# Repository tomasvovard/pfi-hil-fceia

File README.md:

# OHSIM: simulación en tiempo real de un convertidor buck

Repositorio del Proyecto Final de Ingeniería Electrónica (FCEIA, Universidad Nacional de Rosario) sobre la puesta en marcha de la plataforma de *hardware-in-the-loop* **OHSIM** y su validación con un modelo de convertidor buck.

OHSIM es una placa con una FPGA AMD Spartan-7 XC7S50 y DAC de 12 bits, diseñada originalmente por Pablo Trujillo, que ejecuta en tiempo real el modelo de un convertidor de potencia y presenta sus variables como tensiones analógicas. En este trabajo se rediseñó y fabricó la placa, se implementó en la FPGA un modelo no ideal del buck (pérdidas e inductancia dependiente de la corriente, paso de 200 ns), se automatizaron los ensayos con una LaunchPad F28379D y se comparó la respuesta de OHSIM con la del modelo simulado en Simulink y con la del convertidor real del laboratorio (CEuP). En el ensayo E1a, el fit de v<sub>o</sub> entre OHSIM y el modelo es de 93,5 %, y entre OHSIM y el convertidor real, de 83,4 %.

## Contenido

| Carpeta | Contenido | Herramientas |
|---|---|---|
| [`hardware/`](hardware/) | Proyecto KiCad de la placa (esquemáticos 3.2, PCB 3.0) y salidas de fabricación | KiCad 9.0 |
| [`fpga/`](fpga/) | Modelo del buck en Verilog, bancos de prueba, restricciones y scripts de Vivado | Vivado 2025.2, Python 3 |
| [`firmware/`](firmware/) | Firmware de la LaunchPad que genera el PWM y ejecuta los ensayos, y herramientas de la PC | CCS 12.8.1, compilador C2000 22.6.1, PowerShell |
| [`matlab/`](matlab/) | Modelo de referencia en Simulink, generador de coeficientes y procesamiento de capturas | MATLAB R2024b, Simulink 24.2 |
| [`data/`](data/) | Capturas del ensayo E1a (CEuP y OHSIM) | |

Cada carpeta tiene su README con el contenido, los pasos de uso y el resultado esperado.

El archivo de configuración de la FPGA utilizado en los ensayos (`.bit`), el archivo de sondas del ILA (`.ltx`), los informes de compilación y sus sumas SHA-256 están en el *release* **candidate-2026-09-11**.

## Herramientas y versiones

| Herramienta | Uso |
|---|---|
| KiCad 9.0 | Esquemáticos y PCB |
| Vivado 2025.2 | Simulación, síntesis, implementación, programación de la FPGA e ILA |
| Python 3, sin bibliotecas adicionales | Vectores de referencia de los bancos de prueba y pruebas del host |
| Code Composer Studio 12.8.1, compilador C2000 22.6.1 LTS | Firmware de la LaunchPad (el subconjunto necesario de C2000Ware 5.04 está incluido) |
| Windows PowerShell 5.1 | Ejecución de los ensayos |
| MATLAB R2024b, Simulink 24.2 | Modelo de referencia, coeficientes y procesamiento |
| System Identification Toolbox, Control System Toolbox | Identificación de funciones de transferencia |
| Programador JTAG (Digilent JTAG-HS3) | Programación de la FPGA y descarga del ILA |
| Osciloscopio de cuatro canales | Captura de las salidas de OHSIM y del CEuP |

Una versión distinta puede funcionar, pero conviene verificarla con los bancos de prueba y con el ensayo E1a antes de comparar resultados.

## Inicio rápido

Sin hardware, se puede comprobar el diseño y reproducir el procesamiento:

1. **FPGA**: desde `fpga/`, `vivado -mode batch -source scripts/validate_all.tcl` corre los siete bancos de prueba, que deben informar `PASS`.
2. **MATLAB**: con `matlab/` como carpeta de trabajo, ejecutar `p4_2_comparar_fuentes_sin_offset` y `p6_identificar_ft` sobre las capturas de E1a y comparar con los resultados esperados de [`matlab/README.md`](matlab/README.md#resultados-esperados-con-e1a).
3. **Host**: desde `firmware/`, `py -m unittest discover -s host`.

Con la plataforma, el orden de trabajo es programar la FPGA con el archivo del *release* ([`fpga/`](fpga/README.md#programación-y-captura-con-el-ila)), cargar el firmware en la LaunchPad respetando la secuencia de encendido ([`firmware/`](firmware/README.md)), ejecutar los ensayos con `host/ohsim_run.ps1` y procesar las capturas en [`matlab/`](matlab/).

## Clonar una sola parte

Para descargar solo una carpeta (por ejemplo, `fpga/`) sin el resto del repositorio:

```
git clone --filter=blob:none --sparse https://github.com/tomasvovard/pfi-hil-fceia.git
cd pfi-hil-fceia
git sparse-checkout set fpga
```

Para agregar otra carpeta más tarde, `git sparse-checkout add matlab data`. Sin Git, cada carpeta puede descargarse desde la página del repositorio.

## Autoría y licencias

Autor: Tomás Vovard. El diseño original de OHSIM es de Pablo Trujillo ([controlpaths.com](https://controlpaths.com/)); la procedencia de cada parte y los agradecimientos están en [`AUTHORS.md`](AUTHORS.md).

- Software, scripts, documentación y datos: [MIT](LICENSE).
- Hardware (`hardware/`): [CERN-OHL-S-2.0](hardware/LICENSE).
- Archivos de terceros (C2000Ware de Texas Instruments y bibliotecas de KiCad en `hardware/lib/`): su licencia original.

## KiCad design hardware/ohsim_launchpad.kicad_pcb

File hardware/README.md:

# Hardware: placa OHSIM (Platform Board)

Proyecto KiCad de la placa de simulación en tiempo real (*hardware-in-the-loop*) OHSIM, basada en una FPGA AMD Spartan-7 XC7S50 (encapsulado FTGB196, que admite desde la XC7S15 hasta la XC7S50). La placa tiene 16 salidas analógicas de 12 bits (dos DAC AD5328 de ocho canales con buffers), entradas y salidas digitales y de PWM y un RP2040 para la administración de la plataforma. Se conecta a placas de desarrollo comerciales para ensayar lazos de control sobre modelos de convertidores:

- Arduino MKR / Portenta
- Raspberry Pi Pico (1 y 2)
- Texas Instruments LaunchPad (en este trabajo se usó la LAUNCHXL-F28379D)

| Cara superior | Cara inferior |
|---|---|
|  |  |

## Origen y revisión

El diseño original es la *Platform Board* del proyecto OHSIM (versión 0.1 en su serigrafía) de Pablo Trujillo ([controlpaths.com](https://controlpaths.com/)). Esta carpeta contiene su rediseño, hecho en este proyecto final. La procedencia y las licencias se detallan en [`AUTHORS.md`](../AUTHORS.md).

- **Esquemáticos: revisión 3.2.** Las revisiones 3.1 y 3.2 solo reorganizan los esquemáticos (rótulo, títulos por hoja y hoja raíz) y no cambian el netlist.
- **PCB: revisión 3.0**, la fabricada y ensayada. El PCB de esta carpeta agrega en la serigrafía inferior la leyenda "Basado en el diseño original de Pablo Trujillo (controlpaths.com)". No cambia el cobre y el DRC da los mismos resultados que el de la placa fabricada, por lo que es eléctricamente idéntico.
- Las salidas de [`fabricacion/`](fabricacion/) son las que se enviaron al fabricante para la placa 3.0 y, por lo tanto, **no incluyen esa leyenda**. Para fabricar una placa con la leyenda, regenerarlas desde KiCad (ver [Uso](#uso)).

## Contenido

| Archivo | Contenido |
|---|---|
| `ohsim_launchpad.kicad_pro` | Proyecto KiCad |
| `ohsim_launchpad.kicad_sch` | Hoja raíz (diagrama general) |
| `supply.kicad_sch` | Fuentes de alimentación (3V3, 1V8, 1V0) |
| `fpga_power.kicad_sch` | FPGA: alimentación, configuración y JTAG |
| `fpga_bank.kicad_sch` | FPGA: bancos de E/S |
| `rp2040.kicad_sch` | Microcontrolador RP2040, memoria flash y microSD |
| `dac.kicad_sch`, `dac1.kicad_sch` | DAC 0 y DAC 1 con buffers (AOUT0 a AOUT7 y AOUT8 a AOUT15) |
| `arduino.kicad_sch`, `rp_pico.kicad_sch`, `ti_launchpad.kicad_sch` | Interfaces con las placas de desarrollo |
| `ohsim_launchpad.kicad_pcb` | PCB de cuatro capas |
| `ohsim_rotulo.kicad_wks` | Rótulo de las hojas del esquemático |
| `ohsim_launchpad.pdf` | Esquemáticos en PDF |
| `lib/` | Símbolos, huellas y modelos 3D que no forman parte de las bibliotecas estándar de KiCad (ver [Bibliotecas de terceros](#bibliotecas-de-terceros)) |
| `fabricacion/` | Gerbers y perforaciones (`ohsim_launchpad.zip`), BOM, posiciones de montaje (CPL), designadores y netlist IPC de la placa fabricada |
| `img/` | Renders de la placa y logos usados en la serigrafía |

## Uso

Herramienta: **KiCad 9.0**. Las bibliotecas propias se referencian con `${KIPRJMOD}`, de modo que el proyecto abre desde cualquier ubicación sin configurar rutas. Los modelos 3D estándar se toman de las variables `KICAD8_3DMODEL_DIR` y `KICAD9_3DMODEL_DIR` de la instalación de KiCad. La serigrafía usa la fuente Orbitron; si no está instalada, KiCad la reemplaza en pantalla, pero los Gerbers deben generarse con ella instalada.

1. Abrir `ohsim_launchpad.kicad_pro` con KiCad 9.
2. Para revisar el diseño, correr el ERC en el editor de esquemáticos y el DRC en el editor de PCB. El DRC informa cinco observaciones conocidas y aceptadas (cuatro solapamientos de serigrafía y una huella de tipo pasante con pads SMD) y ningún pad sin conectar.
3. Para regenerar las salidas de fabricación, usar *Archivo → Salidas de fabricación* (Gerber, perforaciones, BOM y posiciones), o desde la línea de comandos:

```
kicad-cli pcb export gerbers -o salidas/ ohsim_launchpad.kicad_pcb
kicad-cli pcb export drill -o salidas/ ohsim_launchpad.kicad_pcb
kicad-cli pcb export pos --format csv --units mm -o salidas/posiciones.csv ohsim_launchpad.kicad_pcb
```

La BOM de `fabricacion/bom.csv` incluye la columna `LCSC Part #` con los números de parte usados en el ensamblado. La FPGA (U1) figura como XC7S50-1FTGB196C, la de la placa ensayada, sin número de parte LCSC; la BOM original del pedido la listaba como XC7S25.

## Historial de revisiones

### 3.2 (esquemáticos)
- Rótulo nuevo, títulos descriptivos por hoja y reorganización visual de la hoja raíz. La hoja de alimentación pasa a formato A4. Sin cambios eléctricos.
- PCB: leyenda de atribución al diseño original en la serigrafía inferior. Sin cambios en el cobre.

### 3.0 (PCB fabricado)
- Se unificaron los encapsulados de los componentes eléctricamente iguales y se rehízo la cara inferior priorizando caminos cortos a GND en los capacitores de desacople.
- Se revisaron y completaron los números de parte LCSC y los encapsulados de todos los componentes.
- Se cableó la señal DONE_RP2040 con R69 (0 Ω, no montada) para futuras versiones del firmware del microcontrolador.
- Se reemplazaron los conectores RJ45 por tiras de pines macho de 2 × 4 con paso de 2,54 mm, con todas las señales analógicas rodeadas por GND.
- Se agregaron puntos de prueba con la distribución de una punta de osciloscopio con resorte de GND (Rigol PVP2350).
- Se quitó el recubrimiento de las vías de PWM y de los buses de tensión para usarlas como puntos de prueba, con vías de GND descubiertas cercanas.
- Se agregó la serigrafía de la Universidad, la Facultad, la cátedra y el autor del rediseño.

### 2
- Pistas de alimentación de la FPGA de 0,2 mm de ancho.
- Huellas de componentes pasivos entre 0603 y 0805.
- Vías reubicadas para que no interfieran con los pads de soldadura.

### 1
- Vías debajo de la FPGA reubicadas para que no interfieran con los pads de soldadura.

## Bibliotecas de terceros

La carpeta `lib/` incluye bibliotecas y modelos de terceros, en su mayoría heredados del diseño original. No están cubiertos por la licencia de esta carpeta y conservan la de su autor:

| Archivos | Origen |
|---|---|
| `arduino-library.kicad_sym`, `arduino-library.pretty/` | Biblioteca KiCad de placas Arduino |
| `ABX00042.kicad_sym`, `MODULE_ABX00042.kicad_mod` | Arduino Portenta H7 (ABX00042, SnapEDA) |
| `MCU_RaspberryPi_and_Boards.kicad_sym`, `MCU_RaspberryPi_and_Boards.pretty/`, `Pico.wrl` | Biblioteca KiCad para Raspberry Pi Pico de Nicolò Carandini |
| `LAUNCHXL-F28379D.kicad_sym`, `MOD_LAUNCHXL-F28379D.kicad_mod` | LaunchPad LAUNCHXL-F28379D de Texas Instruments (SnapEDA) |
| `xilinx7.lib` | Símbolos de la familia Xilinx 7 |
| `DM3AT-SF-PEJM5--3DModel-STEP-418109.STEP` | Modelo de fabricante (Hirose) |
| `LQH3NPN2R2MMEL.step`, `IND_LQH3NPN2R2MMEL.kicad_mod` | Modelo y huella de fabricante (Murata) |

## Licencia

El diseño de hardware de esta carpeta se distribuye bajo la licencia [CERN-OHL-S-2.0](LICENSE). Las bibliotecas de terceros mantienen la suya.

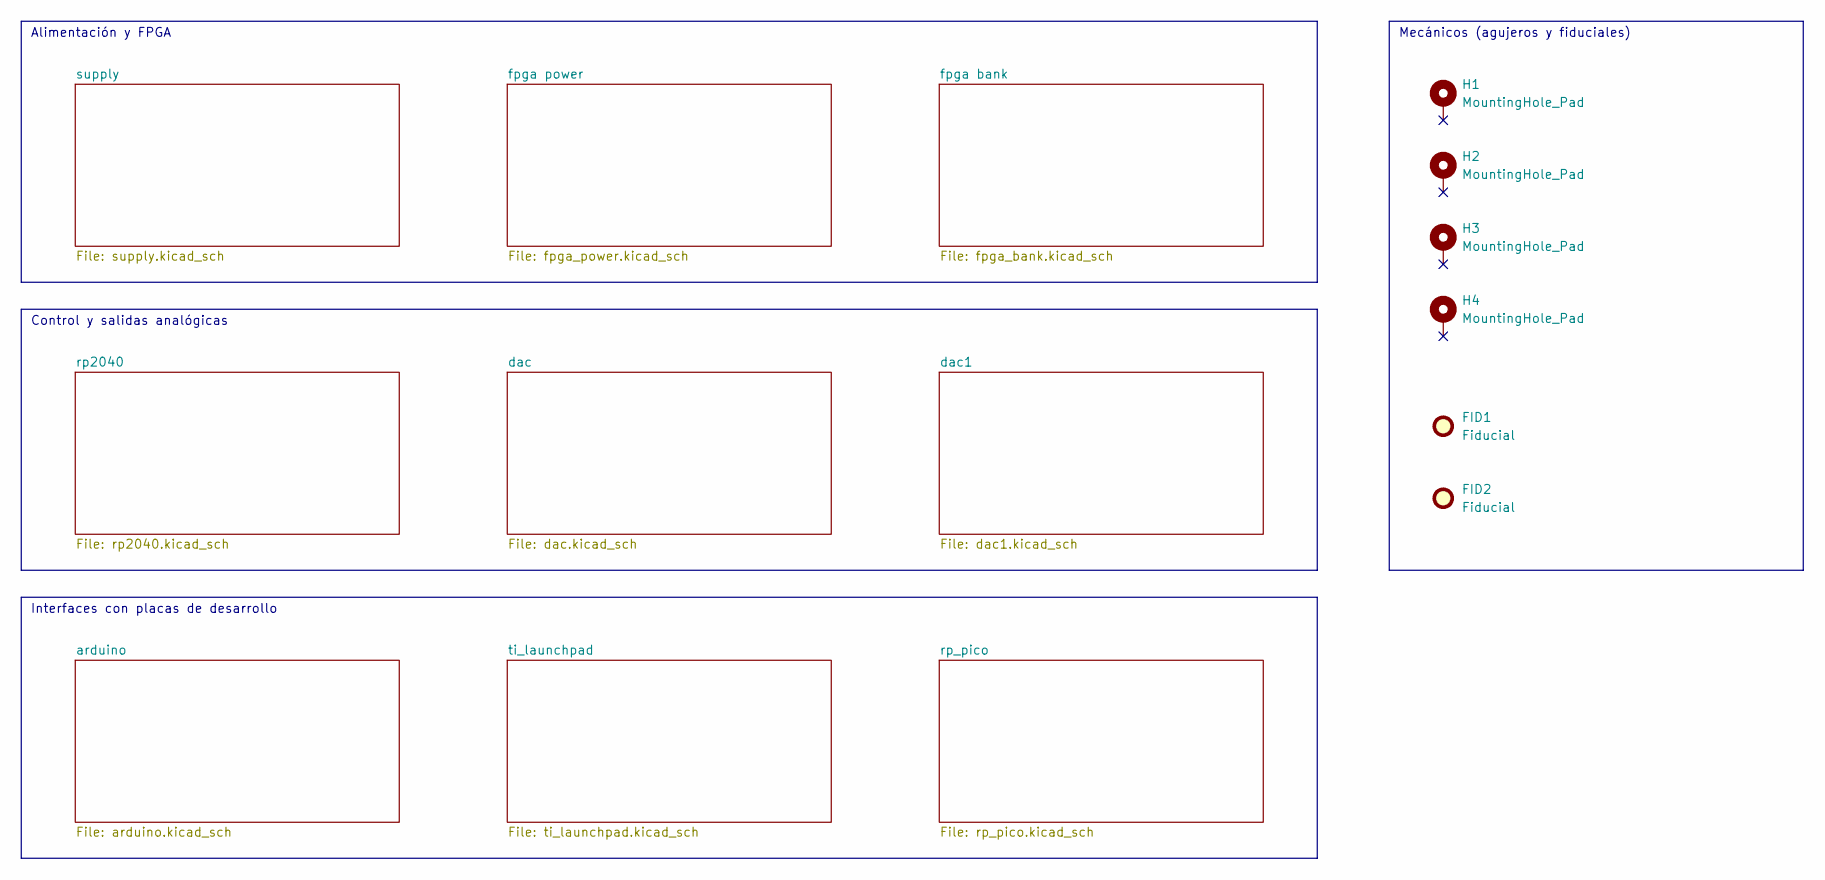
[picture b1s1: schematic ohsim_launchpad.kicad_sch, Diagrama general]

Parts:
FID1, FID2: Fiducial; Fiducial_1mm_Mask2mm
H1, H2, H3, H4: MountingHole_Pad; MountingHole_3.2mm_M3_Pad

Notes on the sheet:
Alimentación y FPGA
Control y salidas analógicas
Interfaces con placas de desarrollo
Mecánicos (agujeros y fiduciales)

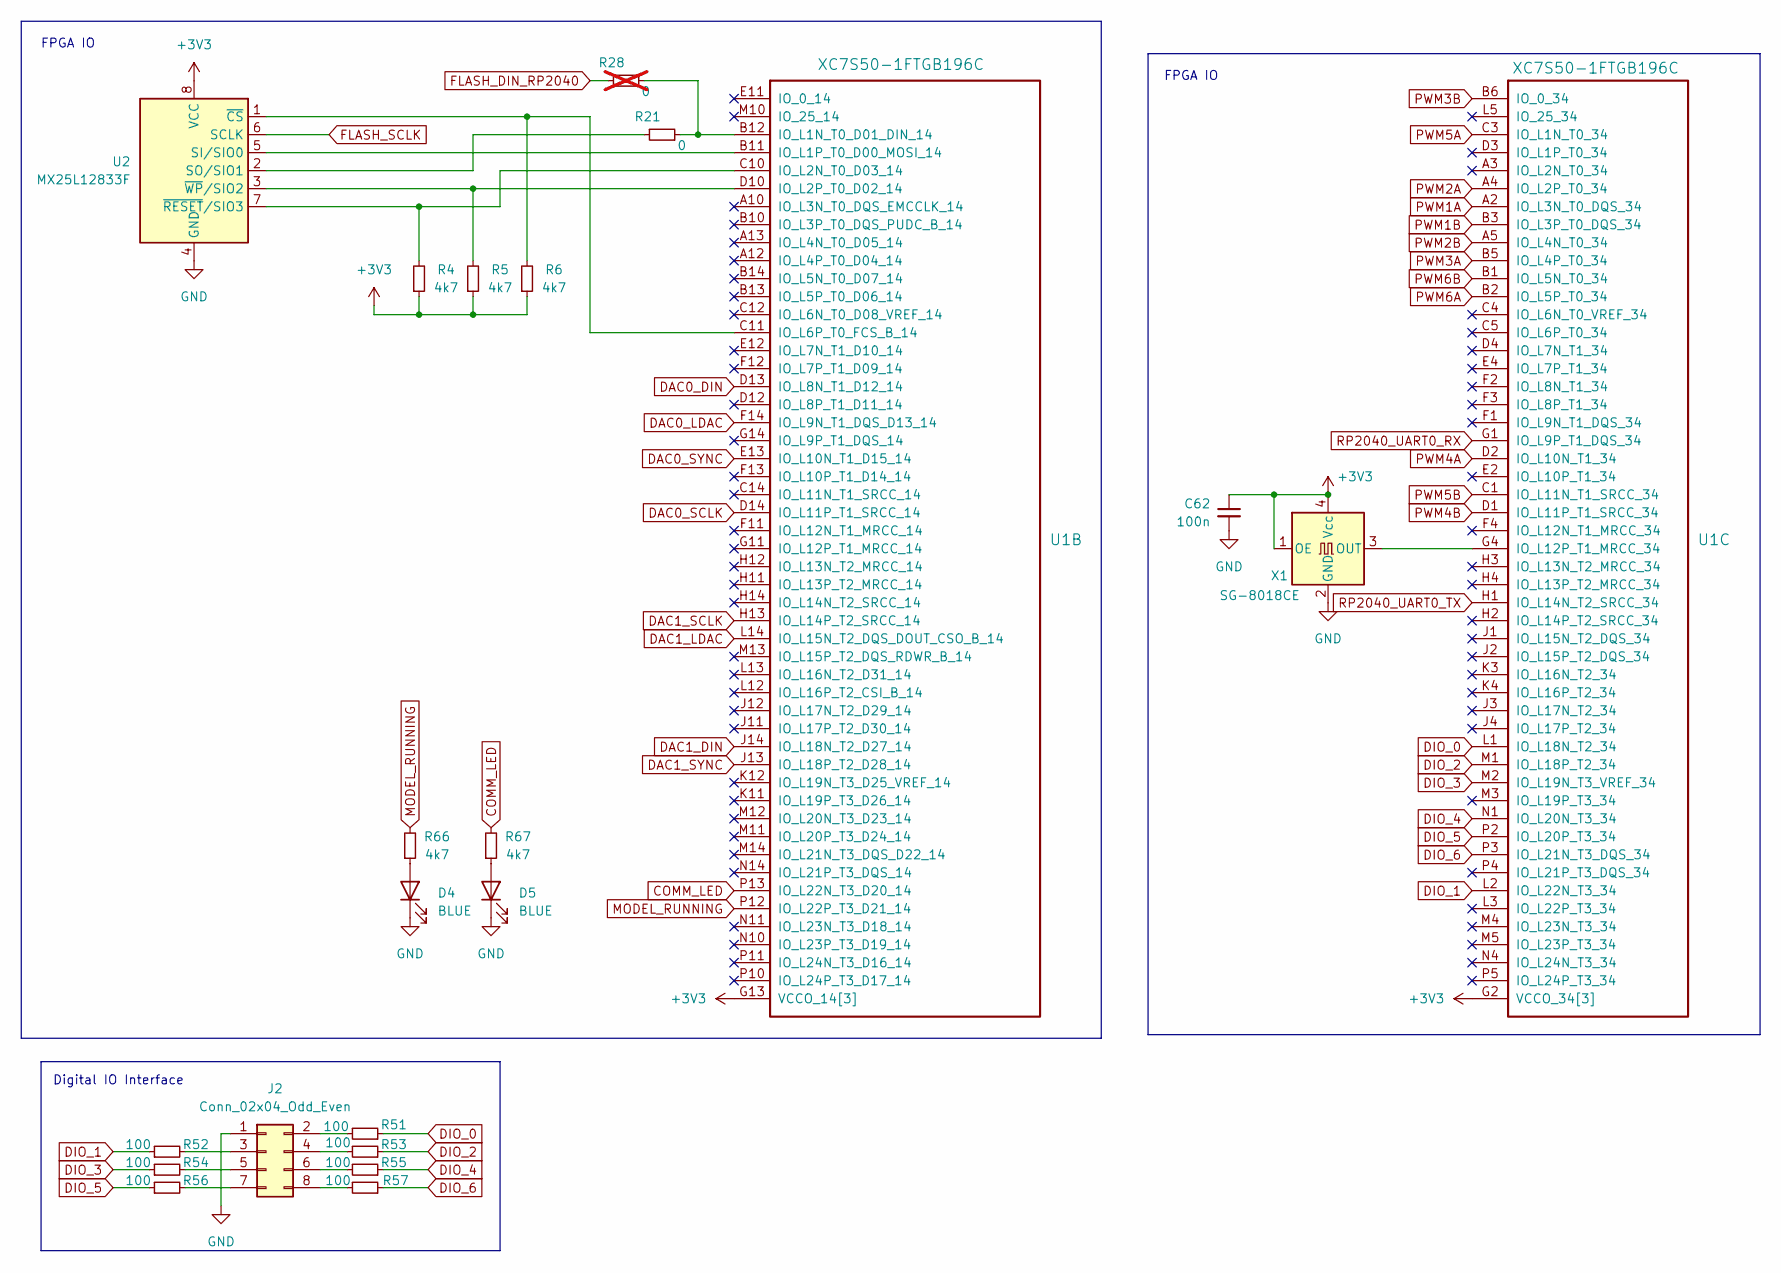
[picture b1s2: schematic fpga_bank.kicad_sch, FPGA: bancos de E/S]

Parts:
C62: 100n; C_0603_1608Metric; JLCPCB C1591
D4, D5: BLUE; LED_0603_1608Metric; JLCPCB C89814
J2: Conn_02x04_Odd_Even; PinHeader_2x04_P2.54mm_Vertical
R4, R5, R6, R66, R67: 4k7; R_0805_2012Metric; JLCPCB C6457904
R21: 0; R_0805_2012Metric; JLCPCB C2907215
R28: 0; R_0805_2012Metric; JLCPCB C2907215; not fitted
R51, R52, R53, R54, R55, R56, R57: 100; R_0805_2012Metric; JLCPCB C2907218
U1: XC7S50-1FTGB196C; Xilinx_FTGB196; JLCPCB Part # C1550986
U2: MX25L12833F; WSON-8-1EP_6x5mm_P1.27mm_EP3.4x4mm; JLCPCB C2802709
X1: SG-8018CE; Crystal_SMD_3225-4Pin_3.2x2.5mm; JLCPCB C390488

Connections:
+3V3: C62.1, R4.1, R5.1, R6.1, U1.G2 (VCCO_34[3]), U1.G13 (VCCO_14[3]), U1.K2 (VCCO_34[3]), U1.K13 (VCCO_14[3]), U1.N2 (VCCO_34[3]), U1.N13 (VCCO_14[3]), U2.8 (VCC), X1.1 (OE), X1.4 (Vcc); also elsewhere on the board
COMM_LED: R67.2, U1.P13 (IO_L22N_T3_D20_14)
DAC0_DIN: U1.D13 (IO_L8N_T1_D12_14); also elsewhere on the board
DAC0_LDAC: U1.F14 (IO_L9N_T1_DQS_D13_14); also elsewhere on the board
DAC0_SCLK: U1.D14 (IO_L11P_T1_SRCC_14); also elsewhere on the board
DAC0_SYNC: U1.E13 (IO_L10N_T1_D15_14); also elsewhere on the board
DAC1_DIN: U1.J14 (IO_L18N_T2_D27_14); also elsewhere on the board
DAC1_LDAC: U1.L14 (IO_L15N_T2_DQS_DOUT_CSO_B_14); also elsewhere on the board
DAC1_SCLK: U1.H13 (IO_L14P_T2_SRCC_14); also elsewhere on the board
DAC1_SYNC: U1.J13 (IO_L18P_T2_D28_14); also elsewhere on the board
DIO_0: R51.1, U1.L1 (IO_L18N_T2_34)
DIO_1: R52.1, U1.L2 (IO_L22N_T3_34)
DIO_2: R53.1, U1.M1 (IO_L18P_T2_34)
DIO_3: R54.1, U1.M2 (IO_L19N_T3_VREF_34)
DIO_4: R55.1, U1.N1 (IO_L20N_T3_34)
DIO_5: R56.1, U1.P2 (IO_L20P_T3_34)
DIO_6: R57.1, U1.P3 (IO_L21N_T3_DQS_34)
FLASH_DIN_RP2040: R28.2; also elsewhere on the board
FLASH_SCLK: U2.6 (SCLK); also elsewhere on the board
GND: C62.2, D4.1 (K), D5.1 (K), J2.1, U2.4 (GND), X1.2 (GND); also elsewhere on the board
MODEL_RUNNING: R66.2, U1.P12 (IO_L22P_T3_D21_14)
unnamed: D4.2 (A), R66.1
unnamed: D5.2 (A), R67.1
unnamed: J2.2, R51.2
unnamed: J2.3, R52.2
unnamed: J2.4, R53.2
unnamed: J2.5, R54.2
unnamed: J2.6, R55.2
unnamed: J2.7, R56.2
unnamed: J2.8, R57.2
unnamed: R21.1, R28.1, U1.B12 (IO_L1N_T0_D01_DIN_14)
unnamed: U1.B11 (IO_L1P_T0_D00_MOSI_14), U2.5 (SI/SIO0)
unnamed: R4.2, U1.C10 (IO_L2N_T0_D03_14), U2.7 (~RESET/SIO3)
unnamed: R5.2, U1.D10 (IO_L2P_T0_D02_14), U2.3 (~WP/SIO2)
unnamed: R6.2, U1.C11 (IO_L6P_T0_FCS_B_14), U2.1 (~CS)
unnamed: U1.G4 (IO_L12P_T1_MRCC_34), X1.3 (OUT)
unnamed: R21.2, U2.2 (SO/SIO1)
PWM1A: U1.A2 (IO_L3N_T0_DQS_34); also elsewhere on the board
PWM1B: U1.B3 (IO_L3P_T0_DQS_34); also elsewhere on the board
PWM2A: U1.A4 (IO_L2P_T0_34); also elsewhere on the board
PWM2B: U1.A5 (IO_L4N_T0_34); also elsewhere on the board
PWM3A: U1.B5 (IO_L4P_T0_34); also elsewhere on the board
PWM3B: U1.B6 (IO_0_34); also elsewhere on the board
PWM4A: U1.D2 (IO_L10N_T1_34); also elsewhere on the board
PWM4B: U1.D1 (IO_L11P_T1_SRCC_34); also elsewhere on the board
PWM5A: U1.C3 (IO_L1N_T0_34); also elsewhere on the board
PWM5B: U1.C1 (IO_L11N_T1_SRCC_34); also elsewhere on the board
PWM6A: U1.B2 (IO_L5P_T0_34); also elsewhere on the board
PWM6B: U1.B1 (IO_L5N_T0_34); also elsewhere on the board
RP2040_UART0_RX: U1.G1 (IO_L9P_T1_DQS_34); also elsewhere on the board
RP2040_UART0_TX: U1.H1 (IO_L14N_T2_SRCC_34); also elsewhere on the board

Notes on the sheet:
FPGA IO
Digital IO Interface

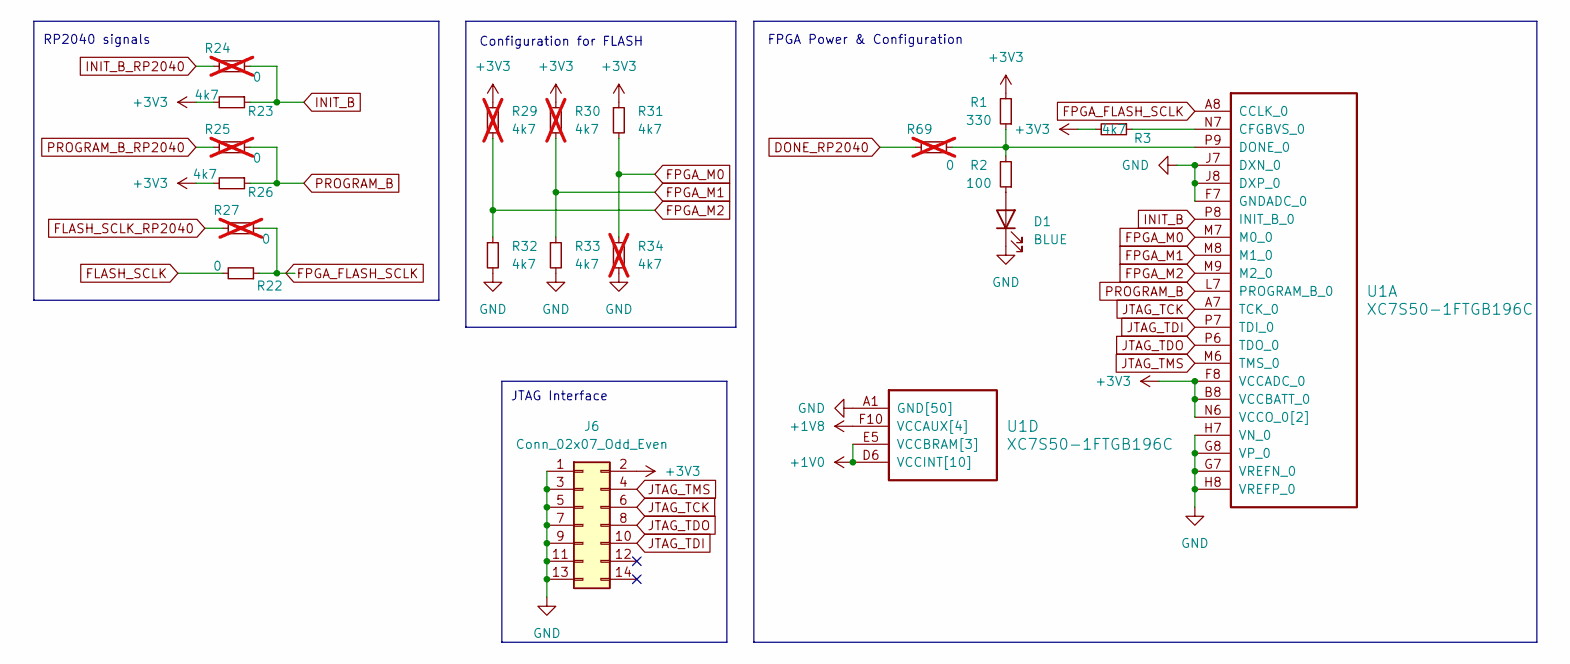
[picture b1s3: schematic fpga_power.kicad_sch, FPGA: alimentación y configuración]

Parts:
D1: BLUE; LED_0603_1608Metric; JLCPCB C89814
J6: Conn_02x07_Odd_Even; PinHeader_2x07_P2.00mm_Vertical_SMD; JLCPCB C19078805
R1: 330; R_0603_1608Metric; JLCPCB C125768
R2: 100; R_0805_2012Metric; JLCPCB C2907218
R3, R23, R26, R31, R32, R33: 4k7; R_0805_2012Metric; JLCPCB C6457904
R22: 0; R_0805_2012Metric; JLCPCB C2907215
R24, R25, R27, R69: 0; R_0805_2012Metric; JLCPCB C2907215; not fitted
R29, R30, R34: 4k7; R_0805_2012Metric; JLCPCB C6457904; not fitted
U1: XC7S50-1FTGB196C; Xilinx_FTGB196; JLCPCB Part # C1550986

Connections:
+1V0: U1.D6 (VCCINT[10]), U1.D8 (VCCINT[10]), U1.E5 (VCCBRAM[3]), U1.E7 (VCCINT[10]), U1.E9 (VCCINT[10]), U1.F6 (VCCINT[10]), U1.G5 (VCCBRAM[3]), U1.G9 (VCCINT[10]), U1.H6 (VCCINT[10]), U1.J5 (VCCBRAM[3]), U1.J9 (VCCINT[10]), U1.K6 (VCCINT[10]), U1.K8 (VCCINT[10]); also elsewhere on the board
+1V8: U1.F10 (VCCAUX[4]), U1.H10 (VCCAUX[4]), U1.K10 (VCCAUX[4]), U1.L9 (VCCAUX[4]); also elsewhere on the board
+3V3: J6.2, R1.2, R3.2, R23.2, R26.2, R29.1, R30.1, R31.1, U1.B8 (VCCBATT_0), U1.F8 (VCCADC_0), U1.N6 (VCCO_0[2]), U1.N8 (VCCO_0[2]); also elsewhere on the board
DONE_RP2040: R69.2; also elsewhere on the board
FLASH_SCLK: R22.2; also elsewhere on the board
FLASH_SCLK_RP2040: R27.2; also elsewhere on the board
FPGA_FLASH_SCLK: R22.1, R27.1, U1.A8 (CCLK_0)
FPGA_M0: R31.2, R34.1, U1.M7 (M0_0)
FPGA_M1: R30.2, R33.1, U1.M8 (M1_0)
FPGA_M2: R29.2, R32.1, U1.M9 (M2_0)
GND: D1.1 (K), J6.1, J6.3, J6.5, J6.7, J6.9, J6.11, J6.13, R32.2, R33.2, R34.2, U1.A1 (GND[50]), U1.A6 (GND[50]), U1.A9 (GND[50]), U1.A11 (GND[50]), U1.A14 (GND[50]), U1.B4 (GND[50]), U1.B7 (GND[50]), U1.B9 (GND[50]), U1.C2 (GND[50]), U1.C6 (GND[50]), U1.C7 (GND[50]), U1.C8 (GND[50]), U1.C9 (GND[50]), U1.C13 (GND[50]), U1.D5 (GND[50]), U1.D7 (GND[50]), U1.D9 (GND[50]), U1.D11 (GND[50]), U1.E1 (GND[50]), U1.E3 (GND[50]), U1.E6 (GND[50]), U1.E8 (GND[50]), U1.E10 (GND[50]), U1.E14 (GND[50]), U1.F5 (GND[50]), U1.F7 (GNDADC_0), U1.F9 (GND[50]), U1.G3 (GND[50]), U1.G6 (GND[50]), U1.G7 (VREFN_0), U1.G8 (VP_0), U1.G10 (GND[50]), U1.G12 (GND[50]), U1.H5 (GND[50]), U1.H7 (VN_0), U1.H8 (VREFP_0), U1.H9 (GND[50]), U1.J6 (GND[50]), U1.J7 (DXN_0), U1.J8 (DXP_0), U1.J10 (GND[50]), U1.K1 (GND[50]), U1.K5 (GND[50]), U1.K7 (GND[50]), U1.K9 (GND[50]), U1.K14 (GND[50]), U1.L4 (GND[50]), U1.L6 (GND[50]), U1.L8 (GND[50]), U1.L10 (GND[50]), U1.L11 (GND[50]), U1.N3 (GND[50]), U1.N5 (GND[50]), U1.N9 (GND[50]), U1.N12 (GND[50]), U1.P1 (GND[50]), U1.P14 (GND[50]); also elsewhere on the board
INIT_B: R23.1, R24.1, U1.P8 (INIT_B_0)
INIT_B_RP2040: R24.2; also elsewhere on the board
JTAG_TCK: J6.6, U1.A7 (TCK_0)
JTAG_TDI: J6.10, U1.P7 (TDI_0)
JTAG_TDO: J6.8, U1.P6 (TDO_0)
JTAG_TMS: J6.4, U1.M6 (TMS_0)
unnamed: D1.2 (A), R2.1
unnamed: R3.1, U1.N7 (CFGBVS_0)
unnamed: R1.1, R2.2, R69.1, U1.P9 (DONE_0)
PROGRAM_B: R25.1, R26.1, U1.L7 (PROGRAM_B_0)
PROGRAM_B_RP2040: R25.2; also elsewhere on the board

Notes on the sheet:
RP2040 signals
Configuration for FLASH
JTAG Interface
FPGA Power & Configuration

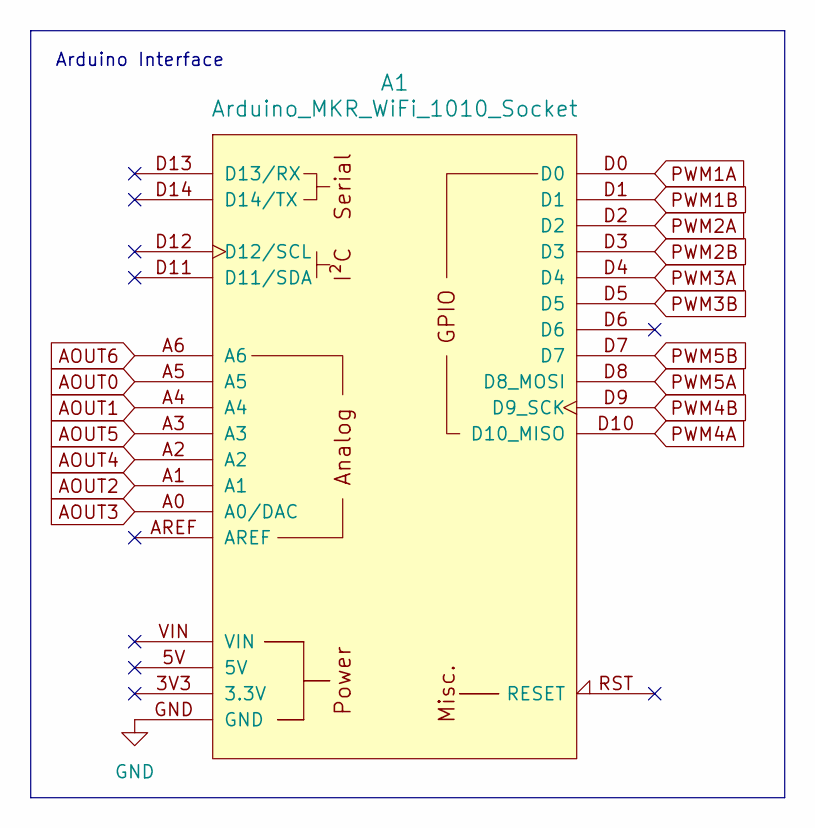
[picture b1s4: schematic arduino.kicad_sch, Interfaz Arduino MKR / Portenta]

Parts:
A1: Arduino_MKR_WiFi_1010_Socket

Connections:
AOUT0: A1.A5; also elsewhere on the board
AOUT1: A1.A4; also elsewhere on the board
AOUT2: A1.A1; also elsewhere on the board
AOUT3: A1.A0 (A0/DAC); also elsewhere on the board
AOUT4: A1.A2; also elsewhere on the board
AOUT5: A1.A3; also elsewhere on the board
AOUT6: A1.A6; also elsewhere on the board
GND: A1.GND; also elsewhere on the board
PWM1A: A1.D0; also elsewhere on the board
PWM1B: A1.D1; also elsewhere on the board
PWM2A: A1.D2; also elsewhere on the board
PWM2B: A1.D3; also elsewhere on the board
PWM3A: A1.D4; also elsewhere on the board
PWM3B: A1.D5; also elsewhere on the board
PWM4A: A1.D10 (D10_MISO); also elsewhere on the board
PWM4B: A1.D9 (D9_SCK); also elsewhere on the board
PWM5A: A1.D8 (D8_MOSI); also elsewhere on the board
PWM5B: A1.D7; also elsewhere on the board

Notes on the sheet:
Arduino Interface

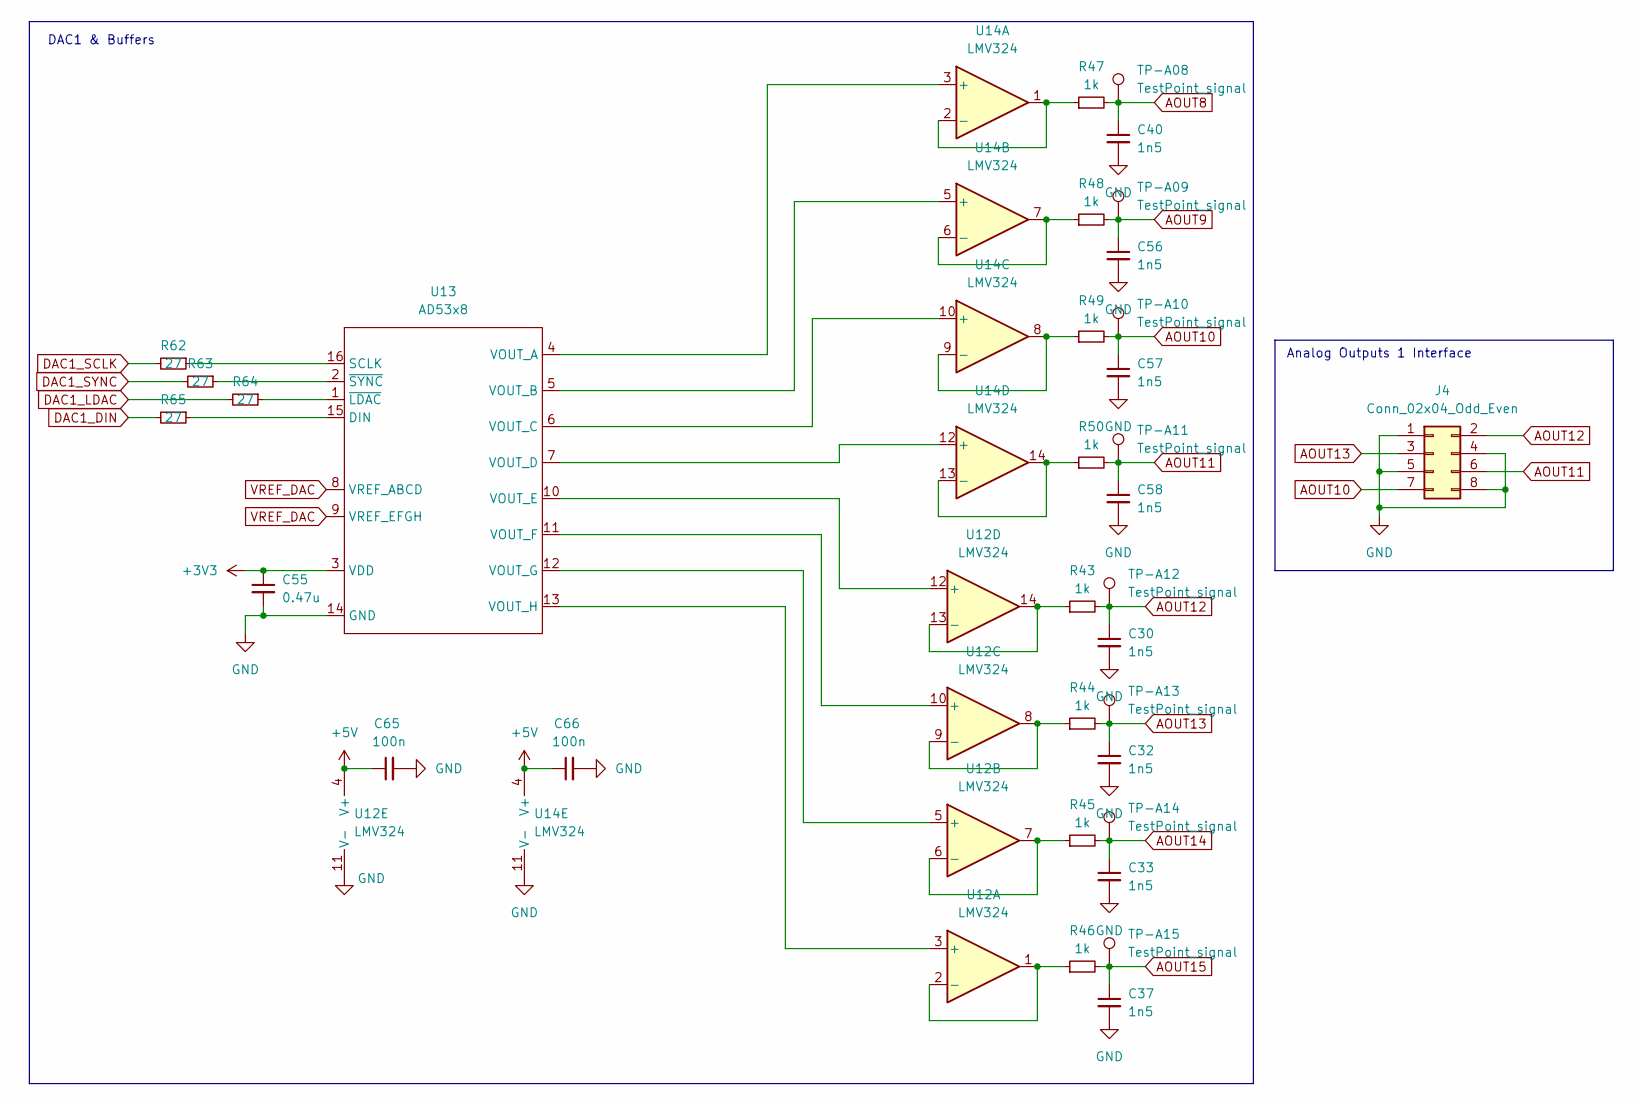
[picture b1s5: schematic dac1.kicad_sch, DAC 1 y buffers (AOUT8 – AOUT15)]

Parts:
C30, C32, C33, C37, C40, C56, C57, C58: 1n5; C_0603_1608Metric; JLCPCB C96090
C55: 0.47u; C_0402_1005Metric; JLCPCB C106255
C65, C66: 100n; C_0603_1608Metric; JLCPCB C1591
J4: Conn_02x04_Odd_Even; PinHeader_2x04_P2.54mm_Vertical
R43, R44, R45, R46, R47, R48, R49, R50: 1k; R_0603_1608Metric; JLCPCB C2907002
R62, R63, R64, R65: 27; R_0603_1608Metric; JLCPCB C25190
TP-A08, TP-A09, TP-A10, TP-A11, TP-A12, TP-A13, TP-A14, TP-A15: TestPoint_signal; TestPoint_THTPad_D1.5mm_Drill0.7mm
U12: LMV324; TSSOP-14_4.4x5mm_P0.65mm; JLCPCB Part # C165067
U13: AD53x8; TSSOP-16_4.4x5mm_P0.65mm; JLCPCB Part # C578186
U14: LMV324; TSSOP-14_4.4x5mm_P0.65mm; JLCPCB C165067

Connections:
+3V3: C55.1, U13.3 (VDD); also elsewhere on the board
+5V: C65.1, C66.1, U12.4 (V+), U14.4 (V+); also elsewhere on the board
AOUT8: C40.1, R47.2, TP-A08.1; also elsewhere on the board
AOUT9: C56.1, R48.2, TP-A09.1; also elsewhere on the board
AOUT10: C57.1, J4.7, R49.2, TP-A10.1; also elsewhere on the board
AOUT11: C58.1, J4.6, R50.2, TP-A11.1; also elsewhere on the board
AOUT12: C30.1, J4.2, R43.2, TP-A12.1; also elsewhere on the board
AOUT13: C32.1, J4.3, R44.2, TP-A13.1; also elsewhere on the board
AOUT14: C33.1, R45.2, TP-A14.1; also elsewhere on the board
AOUT15: C37.1, R46.2, TP-A15.1; also elsewhere on the board
DAC1_DIN: R65.2; also elsewhere on the board
DAC1_LDAC: R64.2; also elsewhere on the board
DAC1_SCLK: R62.2; also elsewhere on the board
DAC1_SYNC: R63.2; also elsewhere on the board
GND: C30.2, C32.2, C33.2, C37.2, C40.2, C55.2, C56.2, C57.2, C58.2, C65.2, C66.2, J4.1, J4.4, J4.5, J4.8, U12.11 (V-), U13.14 (GND), U14.11 (V-); also elsewhere on the board
unnamed: U12.3 (+), U13.13 (VOUT_H)
unnamed: R46.1, U12.1, U12.2 (-)
unnamed: U12.5 (+), U13.12 (VOUT_G)
unnamed: R45.1, U12.6 (-), U12.7
unnamed: U12.10 (+), U13.11 (VOUT_F)
unnamed: R44.1, U12.8, U12.9 (-)
unnamed: U12.12 (+), U13.10 (VOUT_E)
unnamed: R43.1, U12.13 (-), U12.14
unnamed: R65.1, U13.15 (DIN)
unnamed: R62.1, U13.16 (SCLK)
unnamed: U13.4 (VOUT_A), U14.3 (+)
unnamed: U13.5 (VOUT_B), U14.5 (+)
unnamed: U13.6 (VOUT_C), U14.10 (+)
unnamed: U13.7 (VOUT_D), U14.12 (+)
unnamed: R64.1, U13.1 (~LDAC)
unnamed: R63.1, U13.2 (~SYNC)
unnamed: R47.1, U14.1, U14.2 (-)
unnamed: R48.1, U14.6 (-), U14.7
unnamed: R49.1, U14.8, U14.9 (-)
unnamed: R50.1, U14.13 (-), U14.14
VREF_DAC: U13.8 (VREF_ABCD), U13.9 (VREF_EFGH); also elsewhere on the board

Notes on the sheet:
DAC1 & Buffers
Analog Outputs 1 Interface

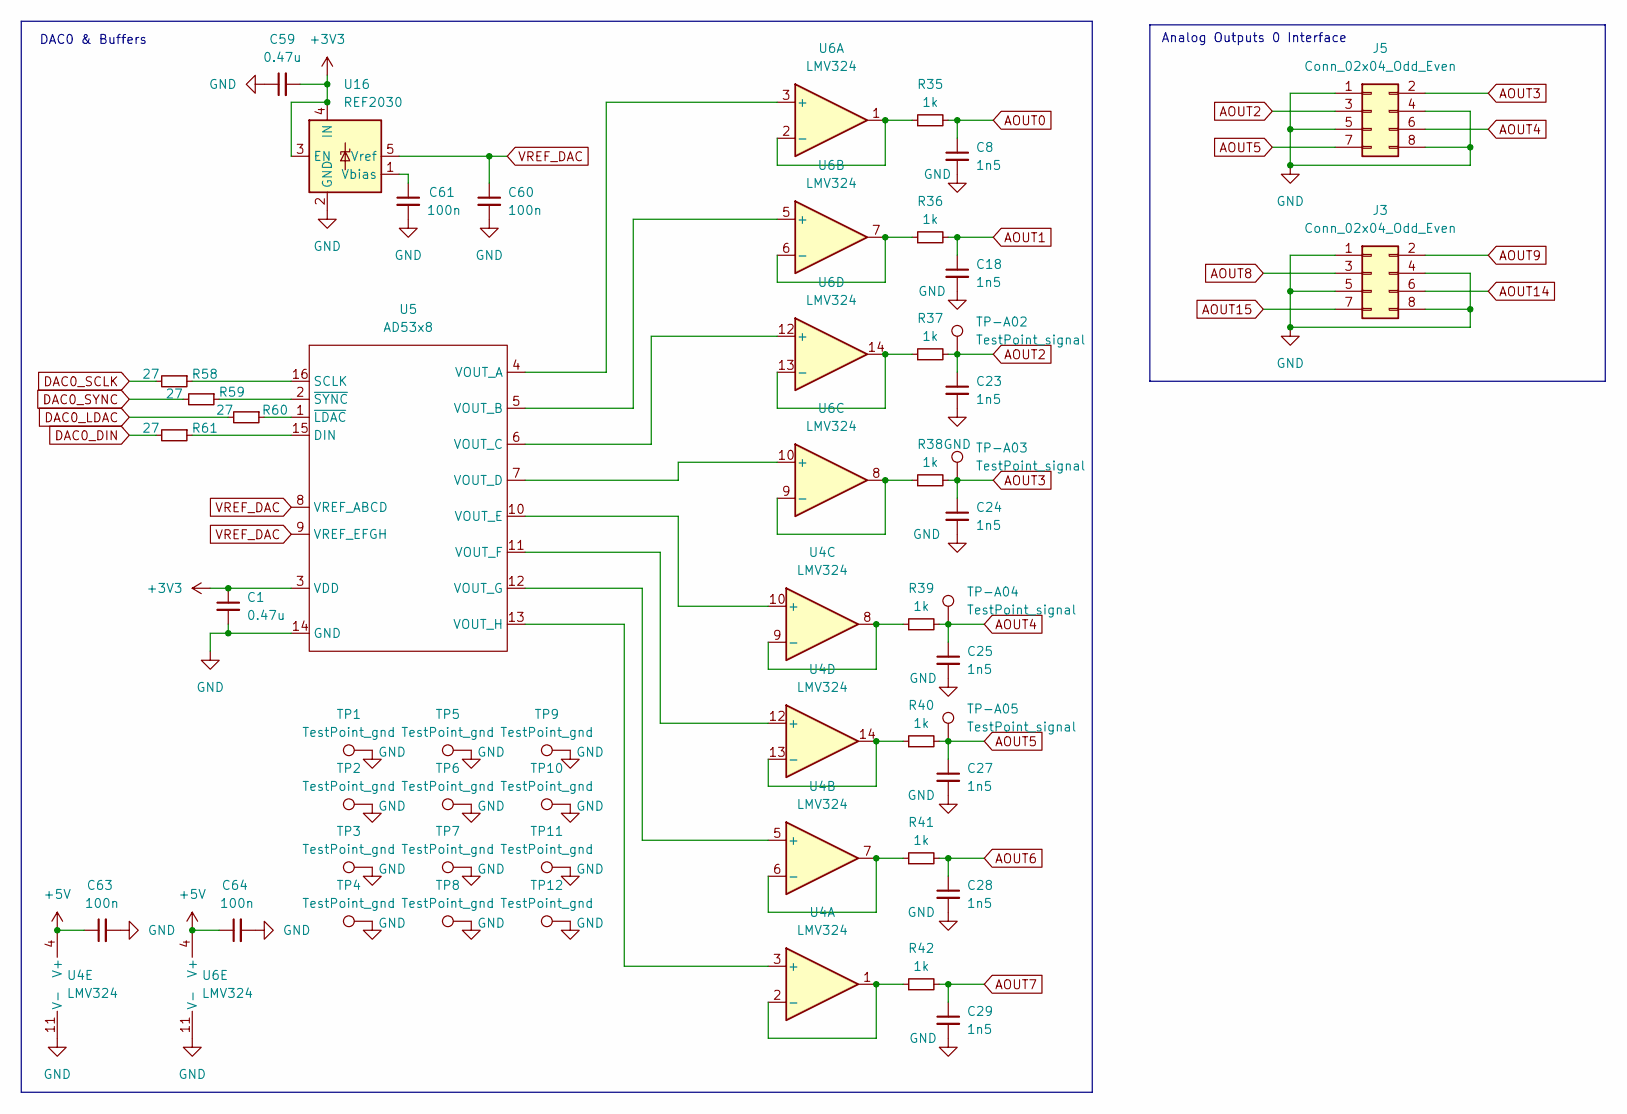
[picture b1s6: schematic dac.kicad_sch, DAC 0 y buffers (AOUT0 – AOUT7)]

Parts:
C1, C59: 0.47u; C_0402_1005Metric; JLCPCB C106255
C8, C18, C23, C24, C25, C27, C28, C29: 1n5; C_0603_1608Metric; JLCPCB C96090
C60, C61, C63, C64: 100n; C_0603_1608Metric; JLCPCB C1591
J3, J5: Conn_02x04_Odd_Even; PinHeader_2x04_P2.54mm_Vertical
R35, R36, R37, R38, R39, R40, R41, R42: 1k; R_0603_1608Metric; JLCPCB C2907002
R58, R59, R60, R61: 27; R_0603_1608Metric; JLCPCB C25190
TP1, TP2, TP3, TP4, TP5, TP6, TP7, TP8, TP9, TP10, TP11, TP12: TestPoint_gnd; TestPoint_THTPad_1.0x1.0mm_Drill0.5mm
TP-A02, TP-A03, TP-A04, TP-A05: TestPoint_signal; TestPoint_THTPad_D1.5mm_Drill0.7mm
U4, U6: LMV324; TSSOP-14_4.4x5mm_P0.65mm; JLCPCB Part # C165067
U5: AD53x8; TSSOP-16_4.4x5mm_P0.65mm; JLCPCB Part # C578186
U16: REF2030; SOT-23-5; JLCPCB Part # C528704

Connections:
+3V3: C1.1, C59.2, U5.3 (VDD), U16.3 (EN), U16.4 (IN); also elsewhere on the board
+5V: C63.1, C64.1, U4.4 (V+), U6.4 (V+); also elsewhere on the board
AOUT0: C8.1, R35.2; also elsewhere on the board
AOUT1: C18.1, R36.2; also elsewhere on the board
AOUT2: C23.1, J5.3, R37.2, TP-A02.1; also elsewhere on the board
AOUT3: C24.1, J5.2, R38.2, TP-A03.1; also elsewhere on the board
AOUT4: C25.1, J5.6, R39.2, TP-A04.1; also elsewhere on the board
AOUT5: C27.1, J5.7, R40.2, TP-A05.1; also elsewhere on the board
AOUT6: C28.1, R41.2; also elsewhere on the board
AOUT7: C29.1, R42.2; also elsewhere on the board
AOUT8: J3.3; also elsewhere on the board
AOUT9: J3.2; also elsewhere on the board
AOUT14: J3.6; also elsewhere on the board
AOUT15: J3.7; also elsewhere on the board
DAC0_DIN: R61.2; also elsewhere on the board
DAC0_LDAC: R60.2; also elsewhere on the board
DAC0_SCLK: R58.2; also elsewhere on the board
DAC0_SYNC: R59.2; also elsewhere on the board
GND: C1.2, C8.2, C18.2, C23.2, C24.2, C25.2, C27.2, C28.2, C29.2, C59.1, C60.2, C61.2, C63.2, C64.2, J3.1, J3.4, J3.5, J3.8, J5.1, J5.4, J5.5, J5.8, TP1.1, TP2.1, TP3.1, TP4.1, TP5.1, TP6.1, TP7.1, TP8.1, TP9.1, TP10.1, TP11.1, TP12.1, U4.11 (V-), U5.14 (GND), U6.11 (V-), U16.2 (GND); also elsewhere on the board
unnamed: U4.3 (+), U5.13 (VOUT_H)
unnamed: R42.1, U4.1, U4.2 (-)
unnamed: U4.5 (+), U5.12 (VOUT_G)
unnamed: R41.1, U4.6 (-), U4.7
unnamed: U4.10 (+), U5.10 (VOUT_E)
unnamed: R39.1, U4.8, U4.9 (-)
unnamed: U4.12 (+), U5.11 (VOUT_F)
unnamed: R40.1, U4.13 (-), U4.14
unnamed: R61.1, U5.15 (DIN)
unnamed: R58.1, U5.16 (SCLK)
unnamed: U5.4 (VOUT_A), U6.3 (+)
unnamed: U5.5 (VOUT_B), U6.5 (+)
unnamed: U5.6 (VOUT_C), U6.12 (+)
unnamed: U5.7 (VOUT_D), U6.10 (+)
unnamed: R60.1, U5.1 (~LDAC)
unnamed: R59.1, U5.2 (~SYNC)
unnamed: R35.1, U6.1, U6.2 (-)
unnamed: R36.1, U6.6 (-), U6.7
unnamed: R38.1, U6.8, U6.9 (-)
unnamed: R37.1, U6.13 (-), U6.14
unnamed: C61.1, U16.1 (Vbias)
VREF_DAC: C60.1, U5.8 (VREF_ABCD), U5.9 (VREF_EFGH), U16.5 (Vref); also elsewhere on the board

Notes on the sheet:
Analog Outputs 0 Interface
DAC0 & Buffers
